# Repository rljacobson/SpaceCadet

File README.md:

# Space Cadet Keyboard Schematic and PCB

This repo contains [KiCAD](https://www.kicad.org/) source files and generated gerber files for the ["Space Cadet" keyboard](https://en.wikipedia.org/wiki/Space-cadet_keyboard), reverse engineered from reference photos in May 2022. To my knowledge, this is the first and only reproduction of this keyboard in EDA form.

<hr>

**Thank you, [PCBWay](https://www.pcbway.com)! They have kindly offered to sponsor the production of a handful of these PCBs. A video review is coming soon!** 

<hr>

### Variants

The board comes in three flavors: 

1. **Main branch:** An attempt at a faithful reproduction of the historic hand-drawn PCB. 
2. **Modern:** The board retains the original topology, and the footprints are in the original positions, but everything is drawn in the style of a modern PCB. 
   
3. **Modern Rounded:** The modern version processed with the *Round Tracks* plugin for KiCAD, which gives the board a hand-drawn aesthetic. 

Variations #2 and #3 are in the Modern branch.

### Reference Material

The design files were reverse engineered from a variety of reference materials. As quality reference materials were hard to get ahold of, I also include them here:

I am unable to find a reference for the entire front of the PCB without the key switches and panel obscuring most of the board. From the traces and vias visible on the back of the PCB,  there are clearly many jumper wires on the front of the PCB the locations of which are easily determined.

## Other interesting things

### Micro Switch SD Series model E footprint and symbol

* [MicroSwitch_SD_Series_E.kicad_sym](MicroSwitch_SD_Series_E.kicad_sym)
* [MicroSwitch_SD_Series_E.kicad_mod](MicroSwitch_SD_Series_E.kicad_mod)

# Open Hardware License

These source files are Copyright © 2022 by Robert Jacobson. They are distributed under the terms of the CERN Open Hardware – Permissive license, also called the CERN-OHL-P v2 license. See [LICENSE.txt](LICENSE.txt) for details.

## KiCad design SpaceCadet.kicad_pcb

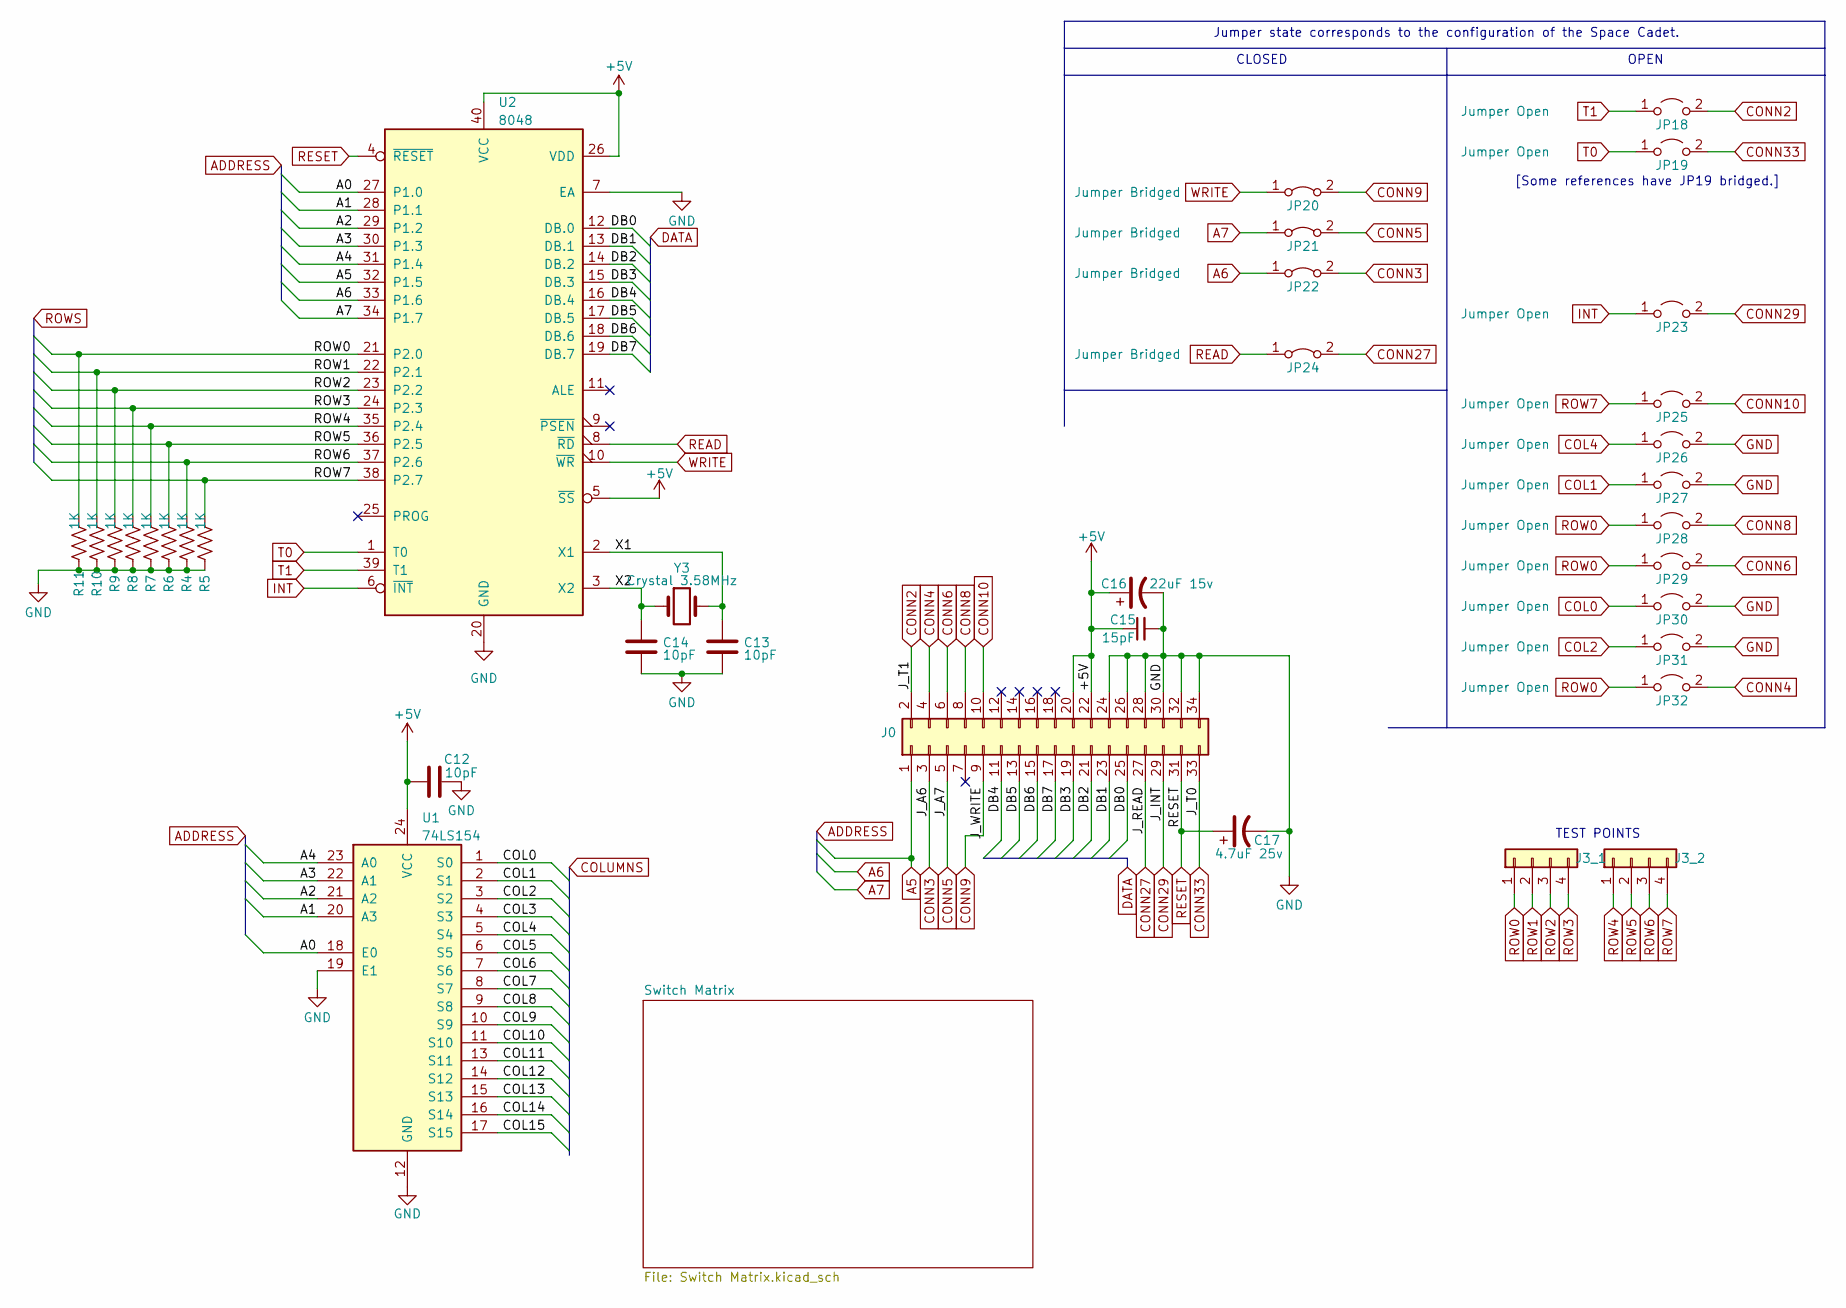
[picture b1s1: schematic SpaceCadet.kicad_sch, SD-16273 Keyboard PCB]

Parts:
C12, C13, C14: 10pF; Two_Pad_Through_Hole_10.4mm
C15: 15pF; Two_Pad_Through_Hole_10.4mm
C16: 22uF 15v; Two_Pad_Through_Hole_20mm
C17: 4.7uF 25v; Two_Pad_Through_Hole_12mm
J0: Conn_02x17_Odd_Even; PinHeader_2x17_P2.54mm_Horizontal
J3_1, J3_2: Conn_01x04; PinHeader_1x04_P2.54mm_Vertical
JP18, JP19, JP23, JP25, JP26, JP27, JP28, JP29, JP30, JP31, JP32: Jumper Open; SolderJumper-2_P1.3mm_Open_TrianglePad1.0x1.5mm
JP20, JP21, JP22, JP24: Jumper Bridged; SolderJumper-2_P1.3mm_Bridged2Bar_Pad1.0x1.5mm
R4, R5, R6, R7, R8, R9, R10, R11: 1K; Two_Pad_Through_Hole_12.4mm
U1: 74LS154; DIP-24_W15.24mm_LongPads
U2: 8048; DIP-40_W15.24mm_Socket_LongPads
Y3: Crystal 3.58MHz; Two_Pad_Through_Hole_10.4mm

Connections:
+5V: C12.1, C15.1, C16.1, J0.20, J0.22, U1.24 (VCC), U2.5 (~SS), U2.26 (VDD), U2.40 (VCC); also elsewhere on the board
/A0: U1.18 (E0), U2.27 (P1.0)
/A1: U1.20 (A3), U2.28 (P1.1)
/A2: U1.21 (A2), U2.29 (P1.2)
/A3: U1.22 (A1), U2.30 (P1.3)
/A4: U1.23 (A0), U2.31 (P1.4)
/COL3: U1.4 (S3)
/COL5: U1.6 (S5)
/COL6: U1.7 (S6)
/COL7: U1.8 (S7)
/COL8: U1.9 (S8)
/COL9: U1.10 (S9)
/COL10: U1.11 (S10)
/COL11: U1.13 (S11)
/COL12: U1.14 (S12)
/COL13: U1.15 (S13)
/COL14: U1.16 (S14)
/COL15: U1.17 (S15)
/DB0: J0.25, U2.12 (DB.0)
/DB1: J0.23, U2.13 (DB.1)
/DB2: J0.21, U2.14 (DB.2)
/DB3: J0.19, U2.15 (DB.3)
/DB4: J0.11, U2.16 (DB.4)
/DB5: J0.13, U2.17 (DB.5)
/DB6: J0.15, U2.18 (DB.6)
/DB7: J0.17, U2.19 (DB.7)
/X1: C13.1, U2.2 (X1), Y3.2
/X2: C14.1, U2.3 (X2), Y3.1
A5: J0.1, U2.32 (P1.5)
A6: JP22.1 (A), U2.33 (P1.6)
A7: JP21.1 (A), U2.34 (P1.7)
COL0: JP30.1 (A), U1.1 (S0); also elsewhere on the board
COL1: JP27.1 (A), U1.2 (S1); also elsewhere on the board
COL2: JP31.1 (A), U1.3 (S2); also elsewhere on the board
COL4: JP26.1 (A), U1.5 (S4); also elsewhere on the board
CONN2: J0.2, JP18.2 (B)
CONN3: J0.3, JP22.2 (B)
CONN4: J0.4, JP32.2 (B)
CONN5: J0.5, JP21.2 (B)
CONN6: J0.6, JP29.2 (B)
CONN8: J0.8, JP28.2 (B)
CONN9: J0.9, JP20.2 (B)
CONN10: J0.10, JP25.2 (B)
CONN27: J0.27, JP24.2 (B)
CONN29: J0.29, JP23.2 (B)
CONN33: J0.33, JP19.2 (B)
GND: C12.2, C13.2, C14.2, C15.2, C16.2, C17.2, J0.24, J0.26, J0.28, J0.30, J0.32, J0.34, JP26.2 (B), JP27.2 (B), JP30.2 (B), JP31.2 (B), R4.1, R5.1, R6.1, R7.1, R8.1, R9.1, R10.1, R11.1, U1.12 (GND), U1.19 (E1), U2.7 (EA), U2.20 (GND)
INT: JP23.1 (A), U2.6 (~INT)
READ: JP24.1 (A), U2.8 (~RD)
RESET: C17.1, J0.31, U2.4 (~RESET)
ROW0: J3_1.1, JP28.1 (A), JP29.1 (A), JP32.1 (A), R11.2, U2.21 (P2.0); also elsewhere on the board
ROW1: J3_1.2, R10.2, U2.22 (P2.1); also elsewhere on the board
ROW2: J3_1.3, R9.2, U2.23 (P2.2); also elsewhere on the board
ROW3: J3_1.4, R8.2, U2.24 (P2.3); also elsewhere on the board
ROW4: J3_2.1, R7.2, U2.35 (P2.4); also elsewhere on the board
ROW5: J3_2.2, R6.2, U2.36 (P2.5); also elsewhere on the board
ROW6: J3_2.3, R4.2, U2.37 (P2.6); also elsewhere on the board
ROW7: J3_2.4, JP25.1 (A), R5.2, U2.38 (P2.7); also elsewhere on the board
T0: JP19.1 (A), U2.1 (T0)
T1: JP18.1 (A), U2.39 (T1)
WRITE: JP20.1 (A), U2.10 (~WR)

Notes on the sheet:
Jumper state corresponds to the configuration of the Space Cadet.
CLOSED
TEST POINTS
[Some references have JP19 bridged.]
OPEN

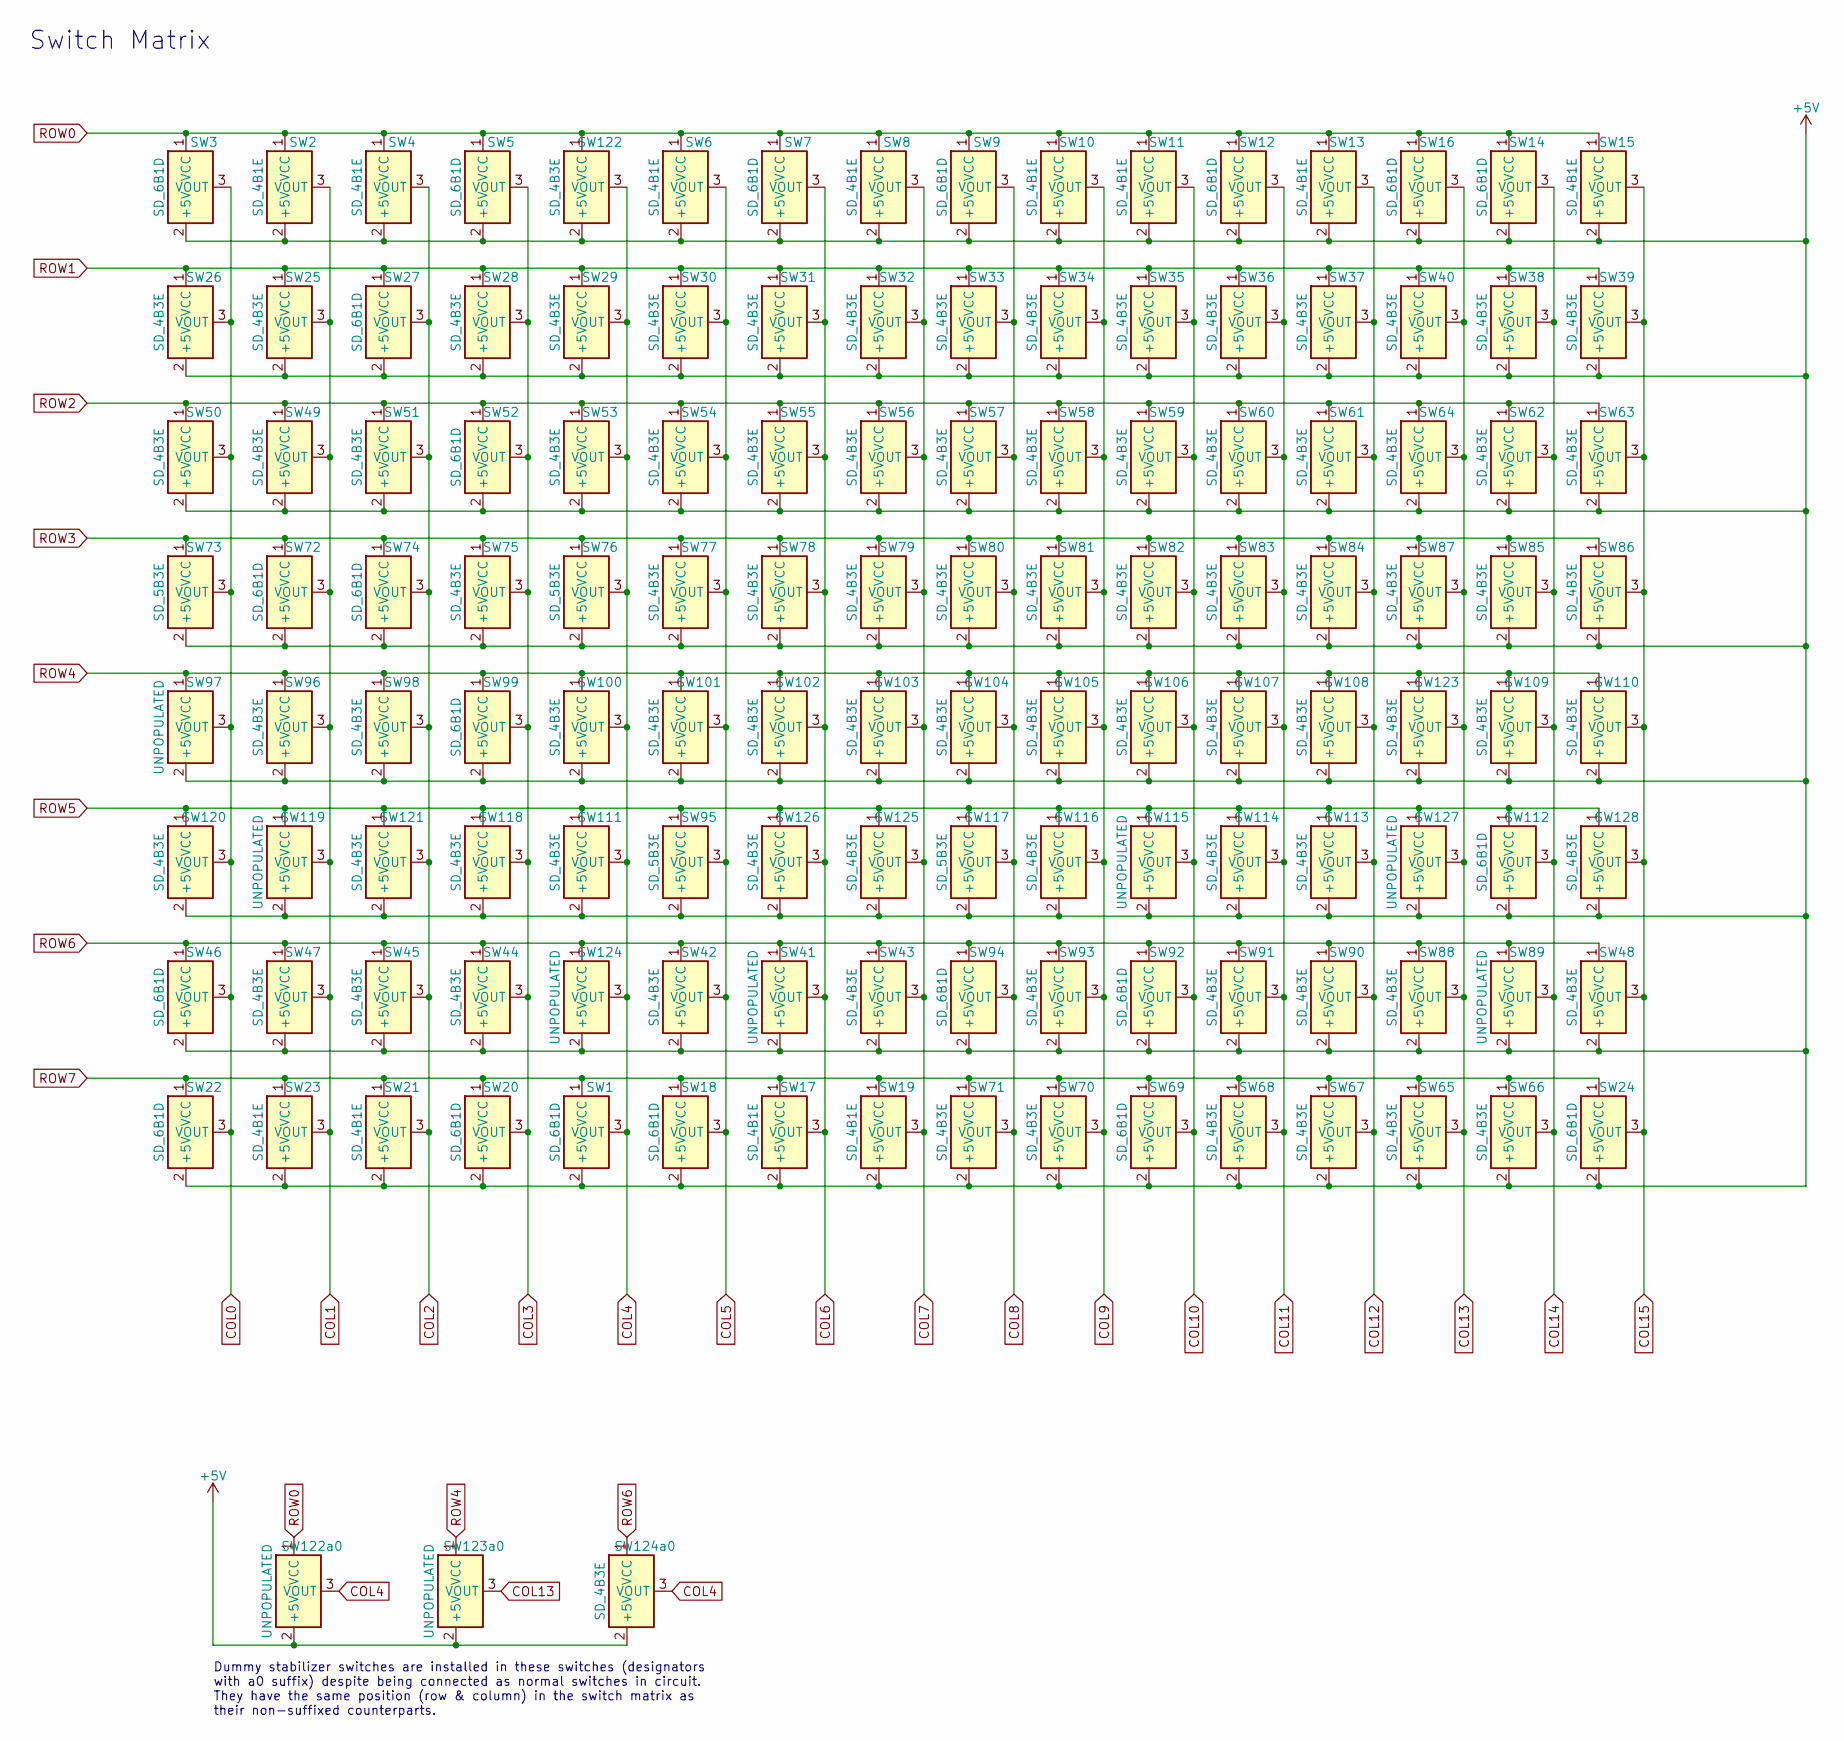
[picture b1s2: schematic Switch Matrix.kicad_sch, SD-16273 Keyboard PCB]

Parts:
SW1, SW3, SW5, SW7, SW9, SW12, SW14, SW16, SW18, SW20, SW22, SW24, SW27, SW46, SW52, SW69, SW72, SW74, SW92, SW94, SW99, SW112: SD_6B1D; MicroSwitch_SD_Series_E
SW2, SW4, SW6, SW8, SW10, SW11, SW13, SW15, SW17, SW19, SW21, SW23: SD_4B1E; MicroSwitch_SD_Series_E
SW25, SW26, SW28, SW29, SW30, SW31, SW32, SW33, SW34, SW35, SW36, SW37, SW38, SW39, SW40, SW42, SW43, SW44, SW45, SW47, SW48, SW49, SW50, SW51, SW53, SW54, SW55, SW56, SW57, SW58, SW59, SW60, SW61, SW62, SW63, SW64, SW65, SW66, SW67, SW68, SW70, SW71, SW75, SW77, SW78, SW79, SW80, SW81, SW82, SW83, SW84, SW85, SW86, SW87, SW88, SW90, SW91, SW93, SW96, SW98, SW100, SW101, SW102, SW103, SW104, SW105, SW106, SW107, SW108, SW109, SW110, SW111, SW113, SW114, SW116, SW118, SW120, SW121, SW122, SW123, SW124a0, SW125, SW126, SW128: SD_4B3E; MicroSwitch_SD_Series_E
SW41, SW89, SW97, SW115, SW119, SW122a0, SW123a0, SW124, SW127: UNPOPULATED; MicroSwitch_SD_Series_E
SW73, SW76, SW95, SW117: SD_5B3E; MicroSwitch_SD_Series_E

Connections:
+5V: SW1.2 (+5V), SW2.2 (+5V), SW3.2 (+5V), SW4.2 (+5V), SW5.2 (+5V), SW6.2 (+5V), SW7.2 (+5V), SW8.2 (+5V), SW9.2 (+5V), SW10.2 (+5V), SW11.2 (+5V), SW12.2 (+5V), SW13.2 (+5V), SW14.2 (+5V), SW15.2 (+5V), SW16.2 (+5V), SW17.2 (+5V), SW18.2 (+5V), SW19.2 (+5V), SW20.2 (+5V), SW21.2 (+5V), SW22.2 (+5V), SW23.2 (+5V), SW24.2 (+5V), SW25.2 (+5V), SW26.2 (+5V), SW27.2 (+5V), SW28.2 (+5V), SW29.2 (+5V), SW30.2 (+5V), SW31.2 (+5V), SW32.2 (+5V), SW33.2 (+5V), SW34.2 (+5V), SW35.2 (+5V), SW36.2 (+5V), SW37.2 (+5V), SW38.2 (+5V), SW39.2 (+5V), SW40.2 (+5V), SW41.2 (+5V), SW42.2 (+5V), SW43.2 (+5V), SW44.2 (+5V), SW45.2 (+5V), SW46.2 (+5V), SW47.2 (+5V), SW48.2 (+5V), SW49.2 (+5V), SW50.2 (+5V), SW51.2 (+5V), SW52.2 (+5V), SW53.2 (+5V), SW54.2 (+5V), SW55.2 (+5V), SW56.2 (+5V), SW57.2 (+5V), SW58.2 (+5V), SW59.2 (+5V), SW60.2 (+5V), SW61.2 (+5V), SW62.2 (+5V), SW63.2 (+5V), SW64.2 (+5V), SW65.2 (+5V), SW66.2 (+5V), SW67.2 (+5V), SW68.2 (+5V), SW69.2 (+5V), SW70.2 (+5V), SW71.2 (+5V), SW72.2 (+5V), SW73.2 (+5V), SW74.2 (+5V), SW75.2 (+5V), SW76.2 (+5V), SW77.2 (+5V), SW78.2 (+5V), SW79.2 (+5V), SW80.2 (+5V), SW81.2 (+5V), SW82.2 (+5V), SW83.2 (+5V), SW84.2 (+5V), SW85.2 (+5V), SW86.2 (+5V), SW87.2 (+5V), SW88.2 (+5V), SW89.2 (+5V), SW90.2 (+5V), SW91.2 (+5V), SW92.2 (+5V), SW93.2 (+5V), SW94.2 (+5V), SW95.2 (+5V), SW96.2 (+5V), SW97.2 (+5V), SW98.2 (+5V), SW99.2 (+5V), SW100.2 (+5V), SW101.2 (+5V), SW102.2 (+5V), SW103.2 (+5V), SW104.2 (+5V), SW105.2 (+5V), SW106.2 (+5V), SW107.2 (+5V), SW108.2 (+5V), SW109.2 (+5V), SW110.2 (+5V), SW111.2 (+5V), SW112.2 (+5V), SW113.2 (+5V), SW114.2 (+5V), SW115.2 (+5V), SW116.2 (+5V), SW117.2 (+5V), SW118.2 (+5V), SW119.2 (+5V), SW120.2 (+5V), SW121.2 (+5V), SW122.2 (+5V), SW122a0.2 (+5V), SW123.2 (+5V), SW123a0.2 (+5V), SW124.2 (+5V), SW124a0.2 (+5V), SW125.2 (+5V), SW126.2 (+5V), SW127.2 (+5V), SW128.2 (+5V); also elsewhere on the board
COL0: SW3.3 (VOUT), SW22.3 (VOUT), SW26.3 (VOUT), SW46.3 (VOUT), SW50.3 (VOUT), SW73.3 (VOUT), SW97.3 (VOUT), SW120.3 (VOUT); also elsewhere on the board
COL1: SW2.3 (VOUT), SW23.3 (VOUT), SW25.3 (VOUT), SW47.3 (VOUT), SW49.3 (VOUT), SW72.3 (VOUT), SW96.3 (VOUT), SW119.3 (VOUT); also elsewhere on the board
COL2: SW4.3 (VOUT), SW21.3 (VOUT), SW27.3 (VOUT), SW45.3 (VOUT), SW51.3 (VOUT), SW74.3 (VOUT), SW98.3 (VOUT), SW121.3 (VOUT); also elsewhere on the board
COL3: SW5.3 (VOUT), SW20.3 (VOUT), SW28.3 (VOUT), SW44.3 (VOUT), SW52.3 (VOUT), SW75.3 (VOUT), SW99.3 (VOUT), SW118.3 (VOUT)
COL4: SW1.3 (VOUT), SW29.3 (VOUT), SW53.3 (VOUT), SW76.3 (VOUT), SW100.3 (VOUT), SW111.3 (VOUT), SW122.3 (VOUT), SW122a0.3 (VOUT), SW124.3 (VOUT), SW124a0.3 (VOUT); also elsewhere on the board
COL5: SW6.3 (VOUT), SW18.3 (VOUT), SW30.3 (VOUT), SW42.3 (VOUT), SW54.3 (VOUT), SW77.3 (VOUT), SW95.3 (VOUT), SW101.3 (VOUT)
COL6: SW7.3 (VOUT), SW17.3 (VOUT), SW31.3 (VOUT), SW41.3 (VOUT), SW55.3 (VOUT), SW78.3 (VOUT), SW102.3 (VOUT), SW126.3 (VOUT)
COL7: SW8.3 (VOUT), SW19.3 (VOUT), SW32.3 (VOUT), SW43.3 (VOUT), SW56.3 (VOUT), SW79.3 (VOUT), SW103.3 (VOUT), SW125.3 (VOUT)
COL8: SW9.3 (VOUT), SW33.3 (VOUT), SW57.3 (VOUT), SW71.3 (VOUT), SW80.3 (VOUT), SW94.3 (VOUT), SW104.3 (VOUT), SW117.3 (VOUT)
COL9: SW10.3 (VOUT), SW34.3 (VOUT), SW58.3 (VOUT), SW70.3 (VOUT), SW81.3 (VOUT), SW93.3 (VOUT), SW105.3 (VOUT), SW116.3 (VOUT)
COL10: SW11.3 (VOUT), SW35.3 (VOUT), SW59.3 (VOUT), SW69.3 (VOUT), SW82.3 (VOUT), SW92.3 (VOUT), SW106.3 (VOUT), SW115.3 (VOUT)
COL11: SW12.3 (VOUT), SW36.3 (VOUT), SW60.3 (VOUT), SW68.3 (VOUT), SW83.3 (VOUT), SW91.3 (VOUT), SW107.3 (VOUT), SW114.3 (VOUT)
COL12: SW13.3 (VOUT), SW37.3 (VOUT), SW61.3 (VOUT), SW67.3 (VOUT), SW84.3 (VOUT), SW90.3 (VOUT), SW108.3 (VOUT), SW113.3 (VOUT)
COL13: SW16.3 (VOUT), SW40.3 (VOUT), SW64.3 (VOUT), SW65.3 (VOUT), SW87.3 (VOUT), SW88.3 (VOUT), SW123.3 (VOUT), SW123a0.3 (VOUT), SW127.3 (VOUT)
COL14: SW14.3 (VOUT), SW38.3 (VOUT), SW62.3 (VOUT), SW66.3 (VOUT), SW85.3 (VOUT), SW89.3 (VOUT), SW109.3 (VOUT), SW112.3 (VOUT)
COL15: SW15.3 (VOUT), SW24.3 (VOUT), SW39.3 (VOUT), SW48.3 (VOUT), SW63.3 (VOUT), SW86.3 (VOUT), SW110.3 (VOUT), SW128.3 (VOUT)
ROW0: SW2.1 (VCC), SW3.1 (VCC), SW4.1 (VCC), SW5.1 (VCC), SW6.1 (VCC), SW7.1 (VCC), SW8.1 (VCC), SW9.1 (VCC), SW10.1 (VCC), SW11.1 (VCC), SW12.1 (VCC), SW13.1 (VCC), SW14.1 (VCC), SW15.1 (VCC), SW16.1 (VCC), SW122.1 (VCC), SW122a0.1 (VCC); also elsewhere on the board
ROW1: SW25.1 (VCC), SW26.1 (VCC), SW27.1 (VCC), SW28.1 (VCC), SW29.1 (VCC), SW30.1 (VCC), SW31.1 (VCC), SW32.1 (VCC), SW33.1 (VCC), SW34.1 (VCC), SW35.1 (VCC), SW36.1 (VCC), SW37.1 (VCC), SW38.1 (VCC), SW39.1 (VCC), SW40.1 (VCC); also elsewhere on the board
ROW2: SW49.1 (VCC), SW50.1 (VCC), SW51.1 (VCC), SW52.1 (VCC), SW53.1 (VCC), SW54.1 (VCC), SW55.1 (VCC), SW56.1 (VCC), SW57.1 (VCC), SW58.1 (VCC), SW59.1 (VCC), SW60.1 (VCC), SW61.1 (VCC), SW62.1 (VCC), SW63.1 (VCC), SW64.1 (VCC); also elsewhere on the board
ROW3: SW72.1 (VCC), SW73.1 (VCC), SW74.1 (VCC), SW75.1 (VCC), SW76.1 (VCC), SW77.1 (VCC), SW78.1 (VCC), SW79.1 (VCC), SW80.1 (VCC), SW81.1 (VCC), SW82.1 (VCC), SW83.1 (VCC), SW84.1 (VCC), SW85.1 (VCC), SW86.1 (VCC), SW87.1 (VCC); also elsewhere on the board
ROW4: SW96.1 (VCC), SW97.1 (VCC), SW98.1 (VCC), SW99.1 (VCC), SW100.1 (VCC), SW101.1 (VCC), SW102.1 (VCC), SW103.1 (VCC), SW104.1 (VCC), SW105.1 (VCC), SW106.1 (VCC), SW107.1 (VCC), SW108.1 (VCC), SW109.1 (VCC), SW110.1 (VCC), SW123.1 (VCC), SW123a0.1 (VCC); also elsewhere on the board
ROW5: SW95.1 (VCC), SW111.1 (VCC), SW112.1 (VCC), SW113.1 (VCC), SW114.1 (VCC), SW115.1 (VCC), SW116.1 (VCC), SW117.1 (VCC), SW118.1 (VCC), SW119.1 (VCC), SW120.1 (VCC), SW121.1 (VCC), SW125.1 (VCC), SW126.1 (VCC), SW127.1 (VCC), SW128.1 (VCC); also elsewhere on the board
ROW6: SW41.1 (VCC), SW42.1 (VCC), SW43.1 (VCC), SW44.1 (VCC), SW45.1 (VCC), SW46.1 (VCC), SW47.1 (VCC), SW48.1 (VCC), SW88.1 (VCC), SW89.1 (VCC), SW90.1 (VCC), SW91.1 (VCC), SW92.1 (VCC), SW93.1 (VCC), SW94.1 (VCC), SW124.1 (VCC), SW124a0.1 (VCC); also elsewhere on the board
ROW7: SW1.1 (VCC), SW17.1 (VCC), SW18.1 (VCC), SW19.1 (VCC), SW20.1 (VCC), SW21.1 (VCC), SW22.1 (VCC), SW23.1 (VCC), SW24.1 (VCC), SW65.1 (VCC), SW66.1 (VCC), SW67.1 (VCC), SW68.1 (VCC), SW69.1 (VCC), SW70.1 (VCC), SW71.1 (VCC); also elsewhere on the board

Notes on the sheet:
Switch Matrix
Dummy stabilizer switches are installed in these switches (designators with a0 suffix) despite being connected as normal switches in circuit. They have the same position (row & column) in the switch matrix as their non-suffixed counterparts.

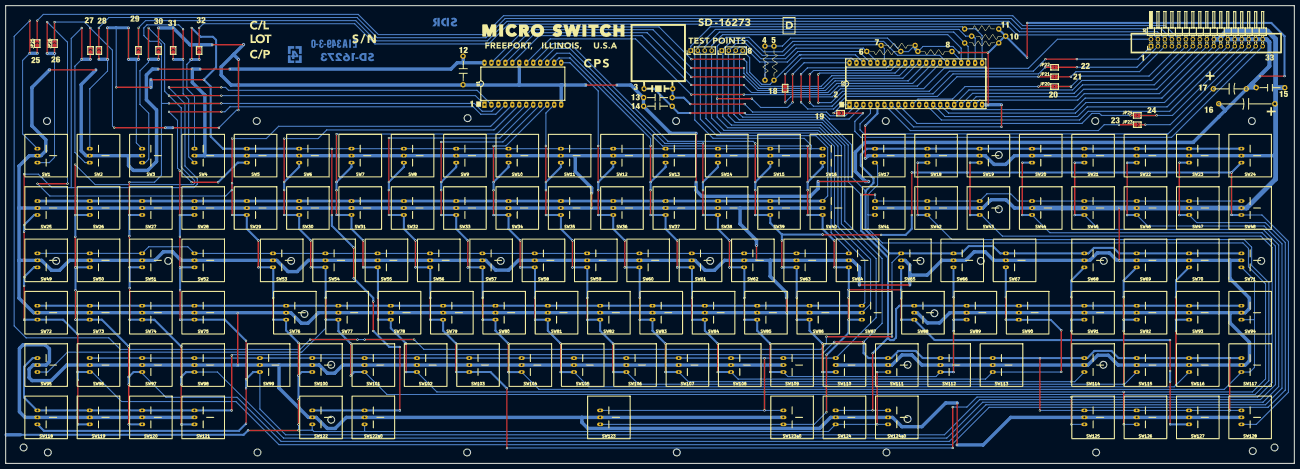
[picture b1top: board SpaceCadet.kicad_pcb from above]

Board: 2 copper layers, 469.0 x 166.6 mm, 166 parts (0 on the bottom side), 61 nets.

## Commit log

2022-05-23 Initial commit.
2022-05-23 Typo.
2022-05-29 Modern EDA route, initial commit.
2022-05-29 Done modern routing.
2022-05-30 Added a rounded tracks version.
2022-06-04 Brought over bug fixes from other branch. Fixed some paths to be closer to original. Fixed path going through mount hole.
2022-06-06 Checkpoint
2022-06-06 Gerbers created.
2022-06-06 ReadMe updated.
2022-06-06 Minor edits
2022-06-13 Added traces, jumpers to front to use DRC. Fixed lots of real and imaginary DRC errors/warnings.
2022-06-13 Now one-sided board.
2022-06-21 Updated the rounded variant.
2022-06-22 Added front-side copper for constraint check. Debugged switch footprint.
2022-06-22 Debugged switch footprint. Adjusted fabrication labels.
2022-06-22 Updated README and image.
2022-06-25 Re-exported gerbers, symbol and footprint. Updated README.md.
2022-06-25 Updated README.
2022-06-25 Regenerated gerbers. Removed DRC-only items.
2022-06-28 Entered correct values for pom pom switches and some others.
2022-06-29 Updated Fab comments and generated new gerbers to reflect fabrication requirements.
2022-08-27 Corrections.
2022-08-27 PCBWay Sponsorship.
2023-01-31 Added BOM generated by InteractiveHtmlBom
